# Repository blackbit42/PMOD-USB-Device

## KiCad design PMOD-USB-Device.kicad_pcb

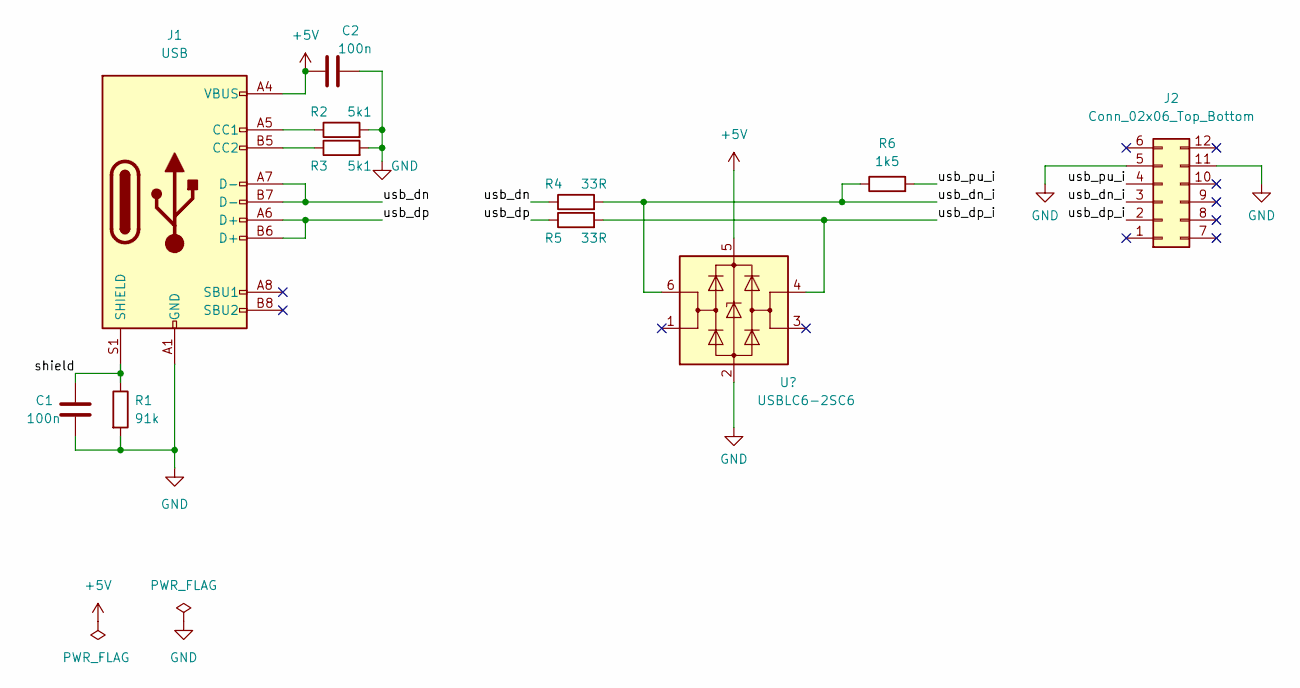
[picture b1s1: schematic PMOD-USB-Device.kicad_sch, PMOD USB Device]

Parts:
C1, C2: 100n; C_0603_1608Metric_Pad1.08x0.95mm_HandSolder; LCSC C1590
J1: USB; USB_C_Receptacle_HRO_TYPE-C-31-M-12; LCSC C165948
J2: Conn_02x06_Top_Bottom; PinHeader_2x06_P2.54mm_Horizontal
R1: 91k; R_0603_1608Metric_Pad0.98x0.95mm_HandSolder; LCSC C23265
R2, R3: 5k1; R_0603_1608Metric_Pad0.98x0.95mm_HandSolder; LCSC C23186
R4, R5: 33R; R_0603_1608Metric_Pad0.98x0.95mm_HandSolder; LCSC C23140
R6: 1k5; R_0603_1608Metric_Pad0.98x0.95mm_HandSolder; LCSC C25867

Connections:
+5V: C2.1, J1.A4 (VBUS), J1.A9 (VBUS), J1.B4 (VBUS), J1.B9 (VBUS); also elsewhere on the board
/shield: C1.1, J1.S1 (SHIELD), R1.1
/usb_dn: J1.A7 (D-), J1.B7 (D-), R4.1
/usb_dn_i: J2.3, R4.2, R6.1; also elsewhere on the board
/usb_dp: J1.A6 (D+), J1.B6 (D+), R5.1
/usb_dp_i: J2.2, R5.2; also elsewhere on the board
/usb_pu_i: J2.4, R6.2
GND: C1.2, C2.2, J1.A1 (GND), J1.A12 (GND), J1.B1 (GND), J1.B12 (GND), J2.5, J2.11, R1.2, R2.2, R3.2; also elsewhere on the board
unnamed: J1.A5 (CC1), R2.1
unnamed: J1.B5 (CC2), R3.1

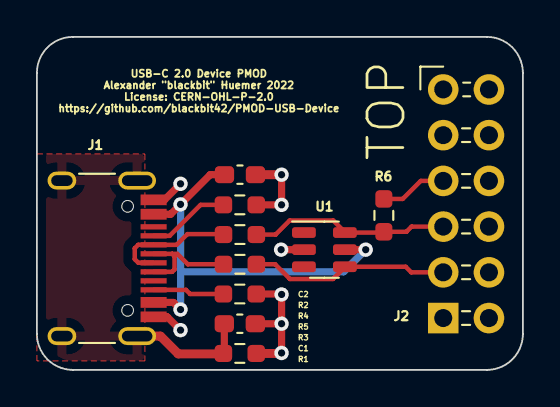
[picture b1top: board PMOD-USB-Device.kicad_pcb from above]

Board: 2 copper layers, 27.0 x 18.5 mm, 11 parts (0 on the bottom side), 10 nets.

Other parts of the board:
U1: USBLC6-2SC6; SOT-23-6

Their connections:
+5V: U1.5 (VBUS); also elsewhere on the board
/usb_dn_i: U1.6 (I/O1); also elsewhere on the board
/usb_dp_i: U1.4 (I/O2); also elsewhere on the board
GND: U1.2 (GND); also elsewhere on the board

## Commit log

2023-01-13 root-commit

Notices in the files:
PMOD-USB-Device.kicad_pcb:
License: CERN-OHL-P-2.0
